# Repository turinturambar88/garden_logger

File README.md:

Garden Logger
=============

This project is a garden logger intented to record various
physical measurements from a home garden.

**This project is a work-in-progress in the early stages of development**

Software Versions
-----------------

avr-gcc 4.8.2
Cadsoft Eagle 7.7

Eagle Libraries
---------------

https://github.com/adafruit/Adafruit-Eagle-Library -- last commit: 4abf84c3856535c0ab6ae96ec4be784d7dcc6b3e
https://github.com/sparkfun/SparkFun-Eagle-Libraries -- last commit: 6ebae9071f809f2e3cb81e523f907661b3316410
https://github.com/turinturambar88/eagle_library
https://github.com/wvanvlaenderen/ESP8266-Eagle_Library 845933428153f5d8eeab9bc1324bed3724700b89

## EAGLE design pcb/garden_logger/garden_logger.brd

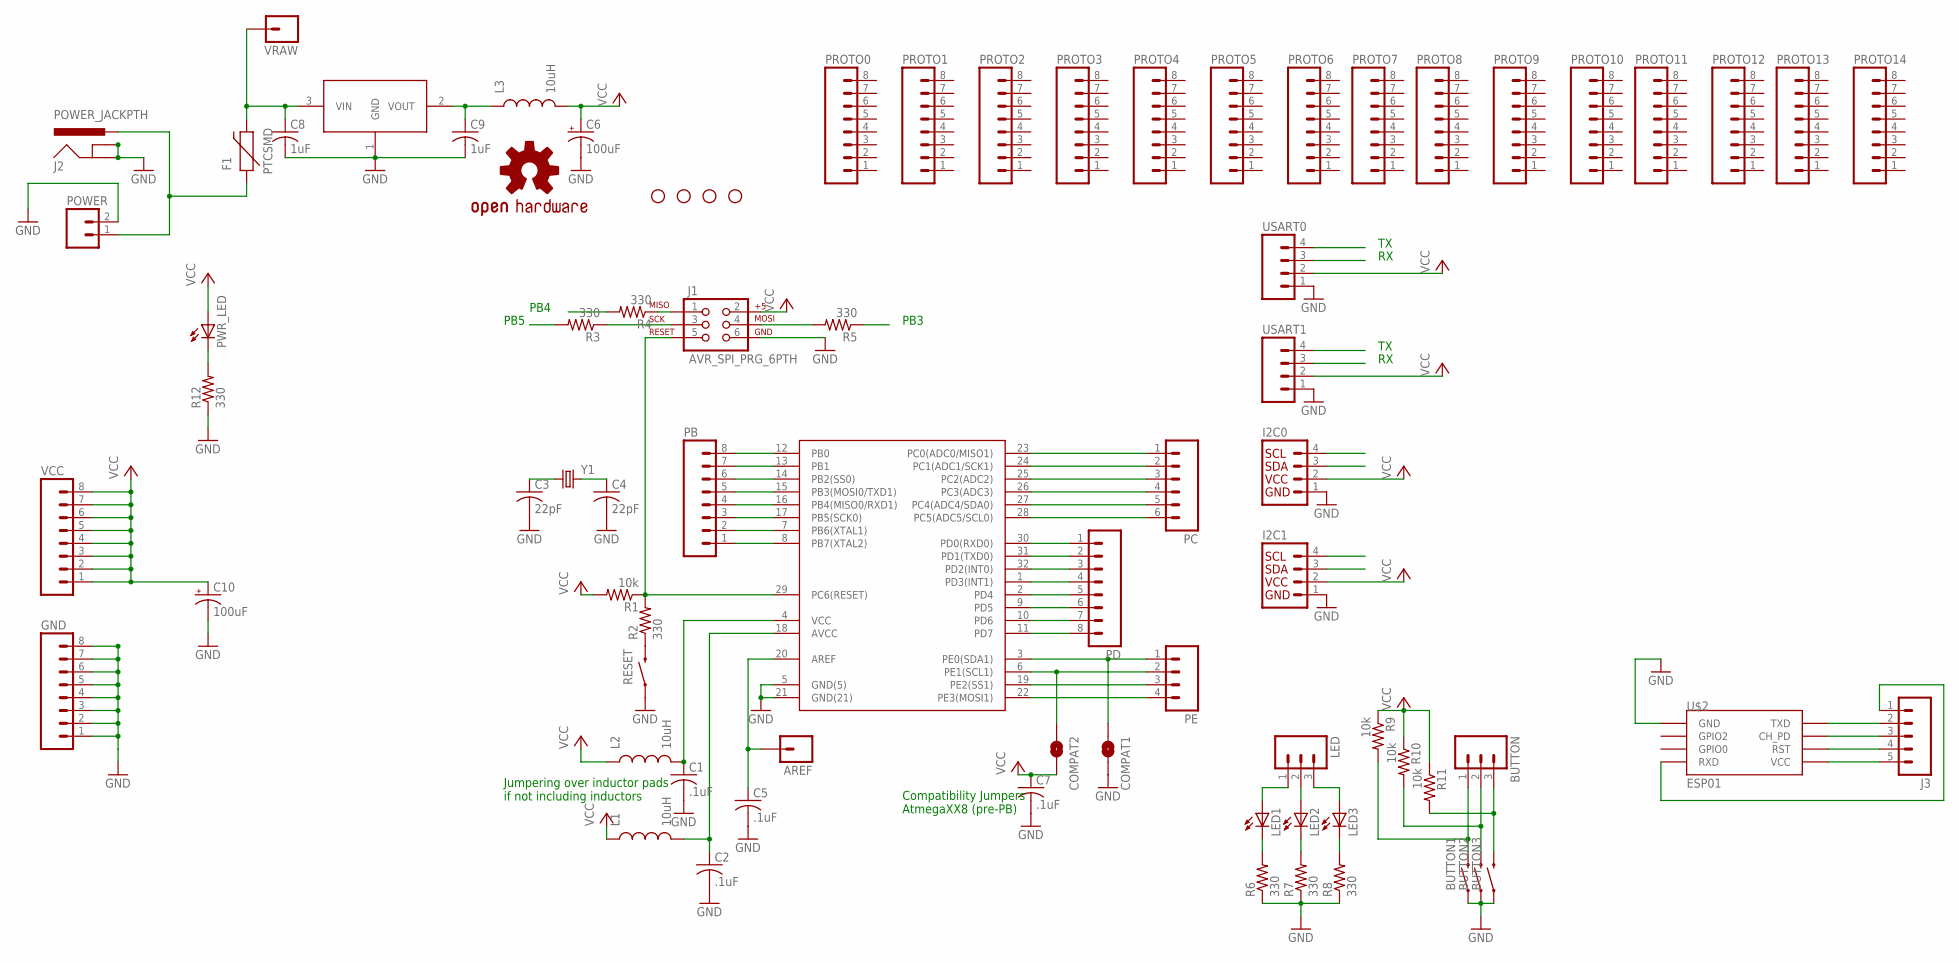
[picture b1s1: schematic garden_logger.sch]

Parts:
AREF: M01PTH; 1X01
BUTTON: M03PTH; 1X03
BUTTON1, BUTTON2, BUTTON3: SWITCH-MOMENTARY-2PTH; TACTILE-PTH
C1, C2, C5, C7: .1uF; C0805
C3, C4: 22pF; C0805
C6, C10: 100uF; CPOL-RADIAL-100UF-25V
C8, C9: 1uF; C0805
COMPAT1, COMPAT2: SOLDERJUMPER-OLDNO; SJ_2S-NO
F1: PTCSMD; PTC-1206
GND: M08; 1X08_ROUND
H1, H2, H3, H4: STAND-OFF
I2C0, I2C1: I2C_STANDARD; 1X04
J1: AVR_SPI_PRG_6PTH; 2X3
J2: POWER_JACKPTH; POWER_JACK_PTH
J3: M05PTH; 1X05
L1, L2, L3: 10uH; 0805
LED: M03PTH; 1X03
LED1, LED2, LED3: LEDCHIPLED_0805; CHIPLED_0805
LOGO1: OSHW-LOGOS; OSHW-LOGO-S
PB: M08; 1X08_ROUND
PC: M06SILK_FEMALE_PTH; 1X06
PD: M08; 1X08_ROUND
PE: M04PTH; 1X04
POWER: M02PTH; 1X02
PROTO0, PROTO1, PROTO2, PROTO3, PROTO4, PROTO5, PROTO6, PROTO7, PROTO8, PROTO9, PROTO10, PROTO11, PROTO12, PROTO13, PROTO14: M08; 1X08_ROUND
PWR_LED: LEDCHIPLED_0805; CHIPLED_0805
R1, R9, R10, R11: 10k; R0805
R2, R3, R4, R5, R6, R7, R8, R12: 330; R0805
RESET: SWITCH-MOMENTARY-2PTH; TACTILE-PTH
U$1: ATMEGA328PB_TQFP; TQFP32-08
U$2: ESP01
U$3: MCP1702; SOT23-3
USART0, USART1: M04PTH; 1X04
VCC: M08; 1X08_ROUND
VRAW: M01PTH; 1X01
Y1: CRYSTALHC49US; HC49US

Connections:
AVCC: C2.1, L1.2, U$1.18 (AVCC)
AVRVCC: C1.1, L2.2, U$1.4 (VCC)
ESP01_CH_PD: J3.3, U$2.CH_PD
ESP01_RST: J3.4, U$2.RST
ESP01_RXD: J3.1, U$2.RX (RXD)
ESP01_TXD: J3.2, U$2.TX (TXD)
ESP01_VCC: J3.5, U$2.VCC
GND: BUTTON1.1, BUTTON2.1, BUTTON3.1, C1.2, C2.2, C3.2, C4.2, C5.2, C6.2 (-), C7.2, C8.2, C9.2, C10.2 (-), COMPAT1.2, GND.1, GND.2, GND.3, GND.4, GND.5, GND.6, GND.7, GND.8, I2C0.1, I2C1.1, J1.6, J2.GND, J2.GNDBREAK, POWER.2, R6.1, R7.1, R8.1, R12.1, RESET.1, U$1.5 (GND(5)), U$1.21 (GND(21)), U$2.GND, U$3.1 (GND), USART0.1, USART1.1
unnamed: AREF.1, C5.1, U$1.20 (AREF)
unnamed: R2.1, RESET.3 (2)
unnamed: J1.1, R4.1
unnamed: J1.3, R3.1
unnamed: J1.4, R5.2
unnamed: C8.1, F1.2, U$3.3 (VIN), VRAW.1
unnamed: PWR_LED.C, R12.2
unnamed: F1.1, J2.PWR, POWER.1
unnamed: LED1.C, R6.2
unnamed: LED2.C, R7.2
unnamed: LED3.C, R8.2
unnamed: LED.1, LED1.A
unnamed: LED.2, LED2.A
unnamed: LED.3, LED3.A
unnamed: C9.1, L3.1, U$3.2 (VOUT)
unnamed: BUTTON.3, BUTTON3.3 (2), R11.2
unnamed: BUTTON.2, BUTTON2.3 (2), R10.2
unnamed: BUTTON.1, BUTTON1.3 (2), R9.2
PB0: PB.8, U$1.12 (PB0)
PB1: PB.7, U$1.13 (PB1)
PB2: PB.6, U$1.14 (PB2(SS0))
PB3: PB.5, R5.1, U$1.15 (PB3(MOSI0/TXD1)), USART1.4
PB4: PB.4, R4.2, U$1.16 (PB4(MISO0/RXD1)), USART1.3
PB5: PB.3, R3.2, U$1.17 (PB5(SCK0))
PB6: C3.1, PB.2, U$1.7 (PB6(XTAL1)), Y1.1
PB7: C4.1, PB.1, U$1.8 (PB7(XTAL2)), Y1.2
PC0: PC.1, U$1.23 (PC0(ADC0/MISO1))
PC1: PC.2, U$1.24 (PC1(ADC1/SCK1))
PC2: PC.3, U$1.25 (PC2(ADC2))
PC3: PC.4, U$1.26 (PC3(ADC3))
PC4: I2C0.3, PC.5, U$1.27 (PC4(ADC4/SDA0))
PC5: I2C0.4, PC.6, U$1.28 (PC5(ADC5/SCL0))
PC6: J1.5, R1.1, R2.2, U$1.29 (PC6(RESET))
PD0: PD.1, U$1.30 (PD0(RXD0)), USART0.3
PD1: PD.2, U$1.31 (PD1(TXD0)), USART0.4
PD2: PD.3, U$1.32 (PD2(INT0))
PD3: PD.4, U$1.1 (PD3(INT1))
PD4: PD.5, U$1.2 (PD4)
PD5: PD.6, U$1.9 (PD5)
PD6: PD.7, U$1.10 (PD6)
PD7: PD.8, U$1.11 (PD7)
PE0: COMPAT1.1, I2C1.3, PE.1, U$1.3 (PE0(SDA1))
PE1: COMPAT2.1, I2C1.4, PE.2, U$1.6 (PE1(SCL1))
PE2: PE.3, U$1.19 (PE2(SS1))
PE3: PE.4, U$1.22 (PE3(MOSI1))
VCC: C6.1 (+), C7.1, C10.1 (+), COMPAT2.2, I2C0.2, I2C1.2, J1.2, L1.1, L2.1, L3.2, PWR_LED.A, R1.2, R9.1, R10.1, R11.1, USART0.2, USART1.2, VCC.1, VCC.2, VCC.3, VCC.4, VCC.5, VCC.6, VCC.7, VCC.8

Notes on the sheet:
Compatibility Jumpers AtmegaXX8 (pre-PB)
PB3
PB5
PB4
Jumpering over inductor pads if not including inductors

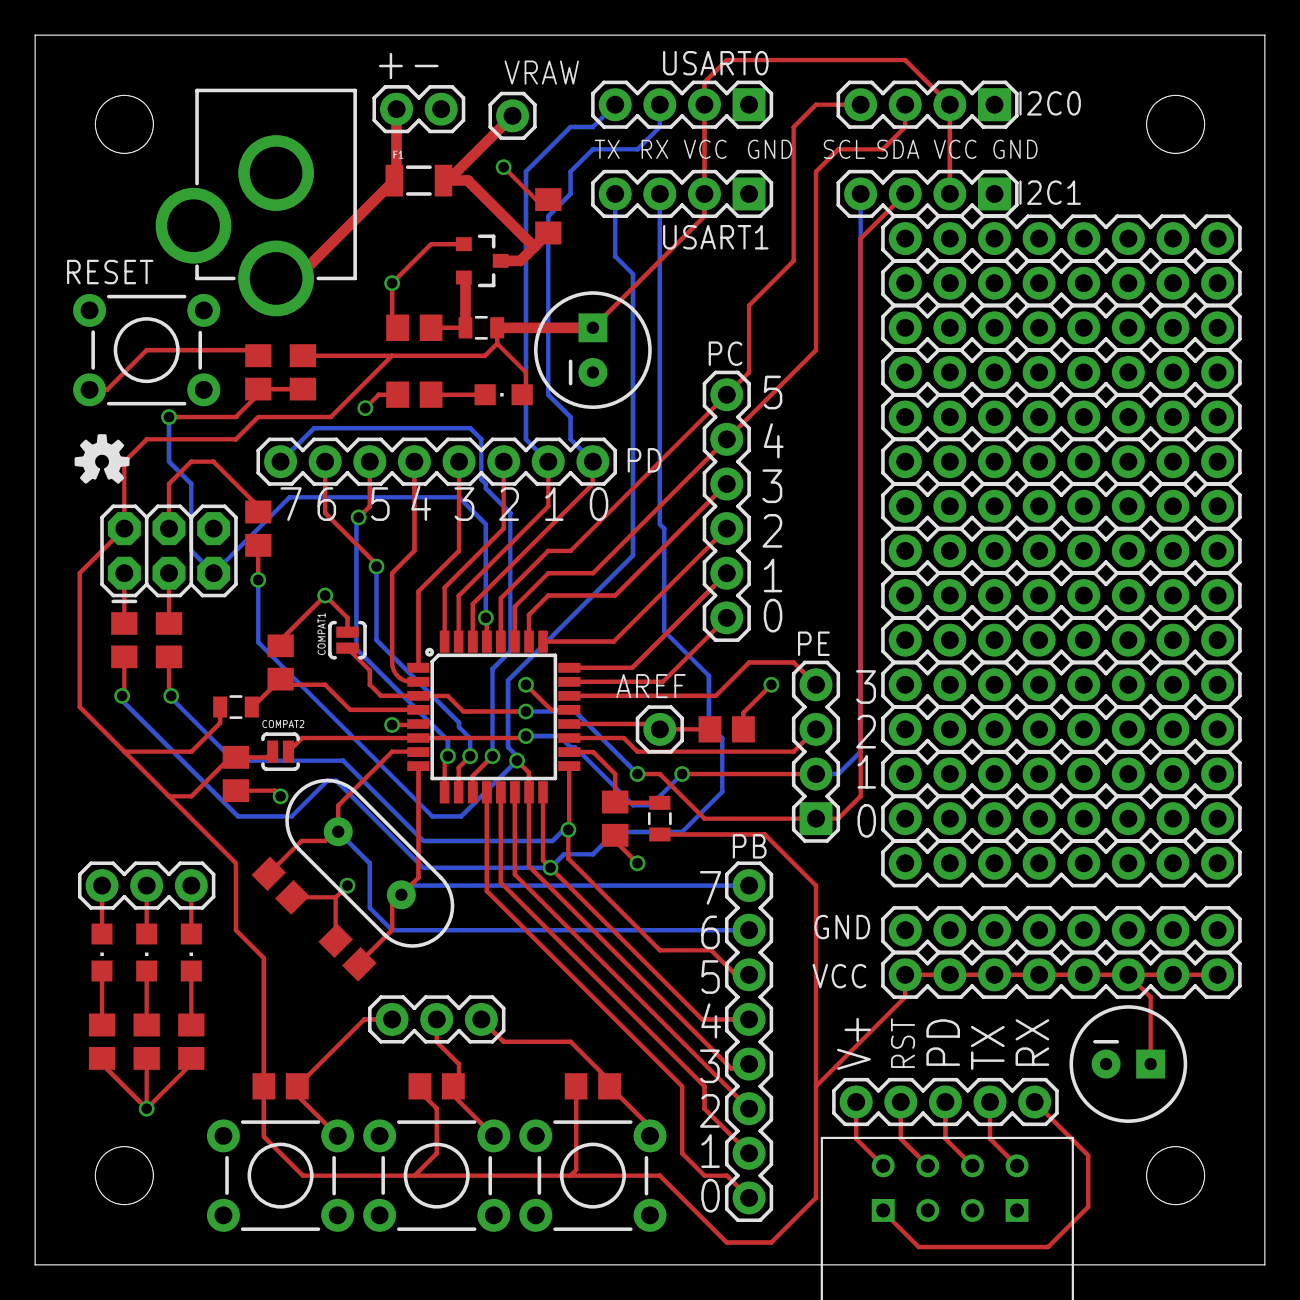
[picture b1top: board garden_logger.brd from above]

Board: 2 copper layers, 70.0 x 70.0 mm, 78 parts (0 on the bottom side), 54 nets.

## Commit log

2016-10-30 empty project layout
2016-10-30 Makefile from AVR Programming book and stripped down main
2016-10-30 ignore avr-gcc generated files
2016-10-30 renamed folders
2016-10-30 empty eagle project
2016-10-30 added software versions
2016-10-31 update make file defaults. create empty lib dir for now
2016-10-31 stubbed out start of util files
2016-10-31 stripped down makefile
2016-11-01 change fuse settings for brown out detect; change CPPFLAGS to CFLAGS
2016-11-01 switch to 8Mhz, no division
2016-11-02 started with usart init and testing loopback
2016-11-02 python serial loopback test
2016-11-16 remove board for now...focus on schematic
2016-11-16 added custom atmega328pb device to empty schematic
2016-11-16 basic support circuit and breakout pin headers
2016-11-17 added some extra breakouts
2016-11-18 most avr stuff connected. working on rpi breakout section. added emtpy board layout
2016-11-18 added buttons and leds. started laying out board
2016-11-25 removed rpi header to have bigger proto area. Mostly done routeing
2016-11-26 finished routing. working on labels
2016-11-27 done with pcb labels

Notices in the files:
parts and their libraries:
SparkFun-Connectors: Licensing: Creative Commons ShareAlike 4.0 International - https://creativecommons.org/licenses/by-sa/4.0
